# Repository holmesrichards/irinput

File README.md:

# Barton IR Input

This is a modified version, in Kosmo format, of the [Barton Musical Circuits 078 IR Input](https://www.bartonmusicalcircuits.com/irin/index.html) synth module. Barton describes the original version as follows:

> This module is designed to allow infrared light sources to interact with your synthesizer. The most common household sources of infrared light are fire and remote controls. Infrared LEDs are also readily available to DIYers who wanted to experiment with creating new devices for controlling synthesizers through this module.

The infrared phototransistor that picks up the IR light may be AC or DC coupled to the circuit. Outputs are a CV proportional to the IR signal and a gate that turns on when the CV rises above a threshold set with a panel pot. Another panel pot sets the phototransistor sensitivity.

Modifications to Barton's design are as follows:

* Added 3.5 mm TRS jack for a cable connecting to an external phototransistor and a switch to select internal or external PT. This allows using candles, lighters, etc. to control the synth while not having to have them right in front of it.
* Added gain knob to control gain of amplifier stage. The sensitivity pot (what Barton calls "bias") does vary the size of the signal but gives a small window between too small (no output) and too large (saturated). In AC coupled mode, the size of the AC component may be small, e.g. a few hundred mV, even when the sensitivity pot is set to just below saturation; of course the AC component disappears if the sensitivity pot is then raised further. The gain pot may be used to amplify the AC component to the level of a few volts. In AC mode, the gain range is 1 to 11. In DC mode, the gain pot may be used to help with faint IR sources; the gain range is 1 to 2.
* Added a bicolor indicator LED for the CV output. Brightness is indicative of CV amplitude and color indicates sign (which is positive in DC mode but can go negative in AC mode). 
* Added an indicator LED for saturation. This turns on when the PT emitter voltage is about 10 V. Normally one would want to operate with the sensitivity pot adjusted to just below where this LED comes on continuously while the IR light source is maximum.
* Specified A1M rather than B1M for sensitivity pot.

My modifications, PCB layout, and documentation are licensed Creative Commons Zero (see [LICENSE](LICENSE)). This license is not intended to apply to Michael Barton's intellectual property and no violation of any applicable copyright is intended. Do not use this design for any commercial purpose without first obtaining Barton's permission.

## Current draw
12 mA +12 V, 8 mA -12 V

## Photos

## Documentation

* [Schematic](Docs/irinput.pdf)
* PCB layout: [front](Docs/_layout_front.pdf), [back](Docs/_layout_back.pdf)
* [BOM](Docs/irinput_bom.md)
* [Build notes](Docs/irinput_build.md)
* [Blog post 1](https://analogoutputblog.wordpress.com/2022/02/22/playing-with-fire/), [blog post 2](https://analogoutputblog.wordpress.com/2022/03/27/ir-input/)

## GitHub repository

* [https://github.com/holmesrichards/irinput](https://github.com/holmesrichards/irinput)

## Submodules

This repo uses submodules aoKicad and Kosmo_panel, which provide needed libaries for KiCad. To clone:

```
git clone git@github.com:holmesrichards/ir_input.git
git submodule init
git submodule update
```

Alternatively do

```
git clone --recurse-submodules git@github.com:holmesrichards/ir_input.git
```

Or if you download the repository as a zip file, you must also click on the "aoKicad" and "Kosmo\_panel" links on the GitHub page (they'll have "@ something" after them) and download them as separate zip files which you can unzip into this repo's aoKicad and Kosmo\_panel directories.

If desired, copy the files from aoKicad and Kosmo\_panel to wherever you prefer (your KiCad user library directory, for instance, if you have one). Then in KiCad, add symbol libraries 

```
aoKicad/ao_symbols
Kosmo_panel/Kosmo
```
and footprint libraries 
```
aoKicad/ao_tht
Kosmo_panel/Kosmo_panel.
```

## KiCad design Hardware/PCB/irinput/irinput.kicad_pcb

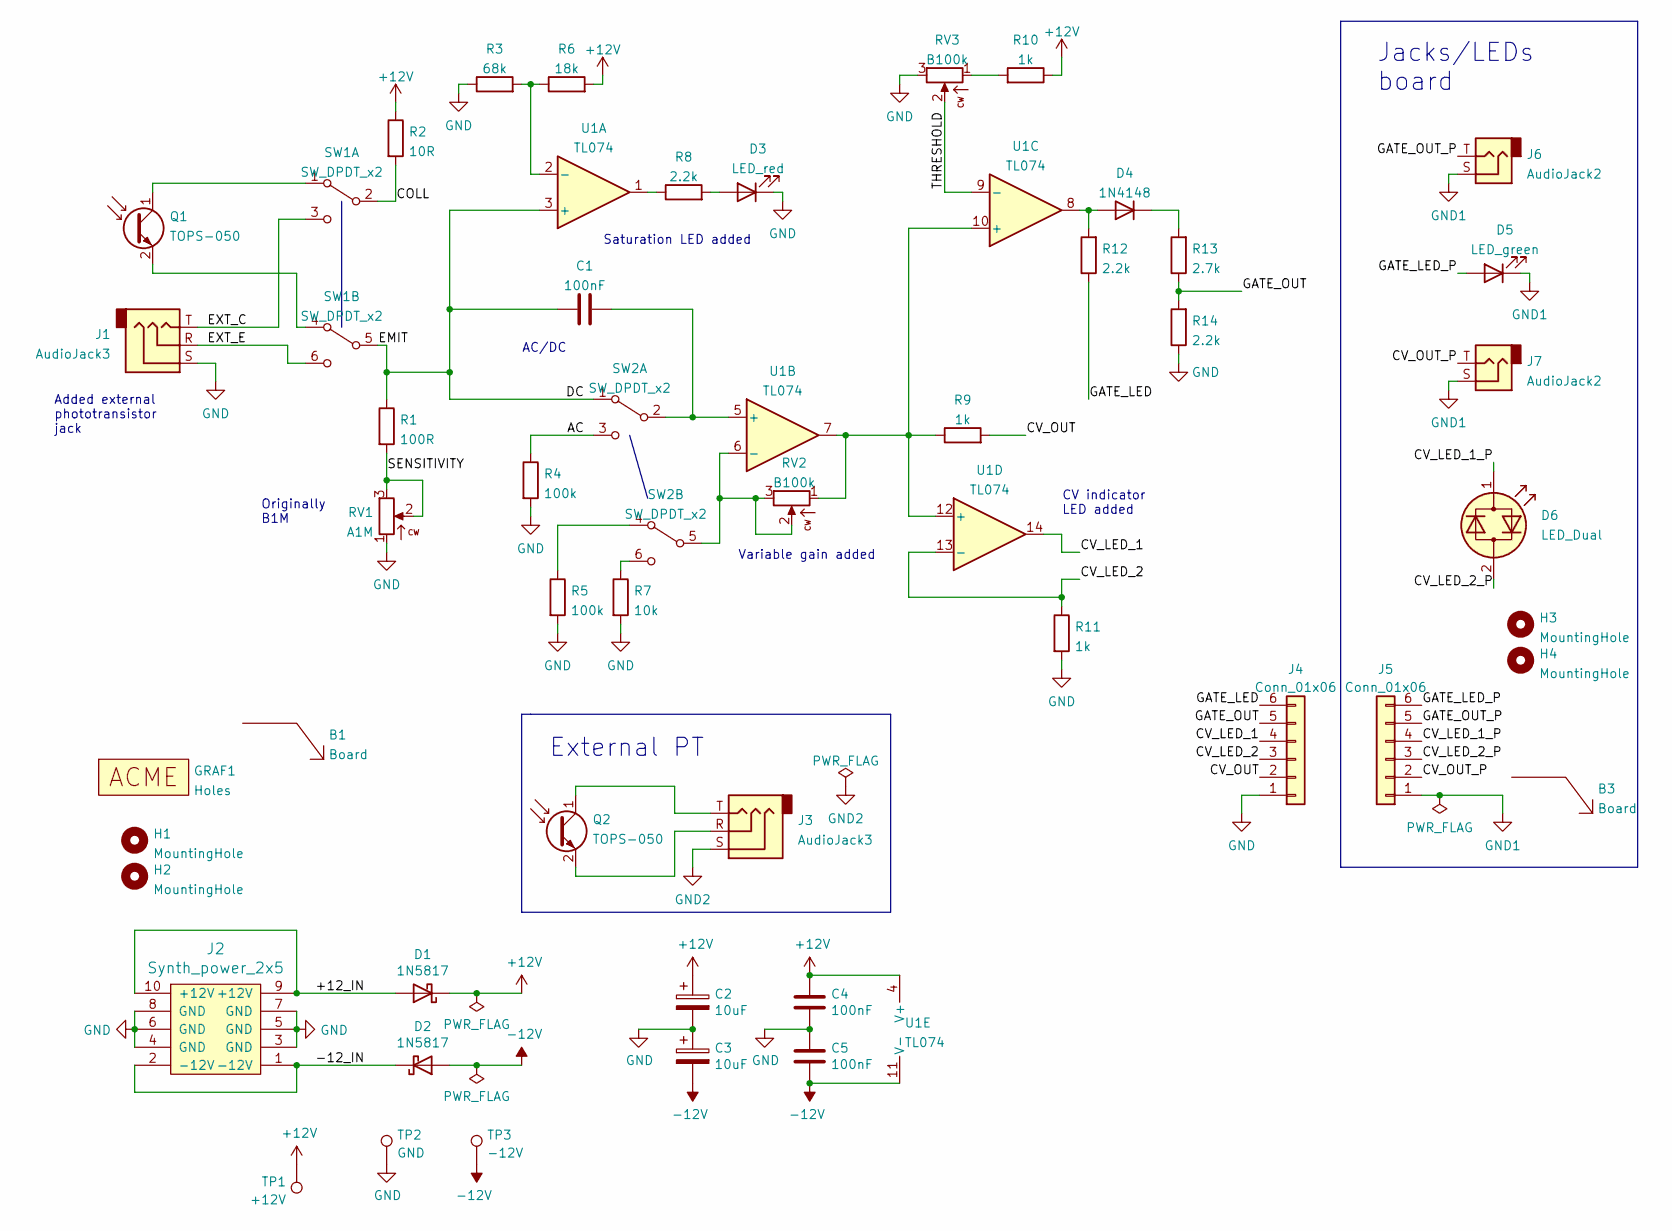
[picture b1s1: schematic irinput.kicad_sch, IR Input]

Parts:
B1, B3: Board; Board_Marker
C1: 100nF; C_Rect_L7.2mm_W2.5mm_P5.00mm_FKS2_FKP2_MKS2_MKP2
C2, C3: 10uF; CP_Radial_D6.3mm_P2.50mm
C4, C5: 100nF; C_Disc_D3.0mm_W1.6mm_P2.50mm
D1, D2: 1N5817; D_DO-41_SOD81_P10.16mm_Horizontal
D3: LED_red; LED_D5.0mm
D4: 1N4148; D_DO-35_SOD27_P7.62mm_Horizontal
D5: LED_green; LED_D5.0mm
D6: LED_Dual; LED_D5.0mm
GRAF1: Holes; irinput_panel_holes
H1, H2, H3, H4: MountingHole; MountingHole_3.2mm_M3
J1, J3: AudioJack3; Jack_3.5mm_PJ-301CM
J2: Synth_power_2x5; Power_Header
J4: Conn_01x06; PinHeader_1x06_P2.54mm_Vertical
J5: Conn_01x06; PinSocket_1x06_P2.54mm_Vertical
J6, J7: AudioJack2; Jack_6.35mm_PJ_629HAN
Q1, Q2: TOPS-050; LED_D5.0mm
R1: 100R; R_Axial_DIN0207_L6.3mm_D2.5mm_P10.16mm_Horizontal
R2: 10R; R_Axial_DIN0207_L6.3mm_D2.5mm_P10.16mm_Horizontal
R3: 68k; R_Axial_DIN0207_L6.3mm_D2.5mm_P10.16mm_Horizontal
R4, R5: 100k; R_Axial_DIN0207_L6.3mm_D2.5mm_P10.16mm_Horizontal
R6: 18k; R_Axial_DIN0207_L6.3mm_D2.5mm_P10.16mm_Horizontal
R7: 10k; R_Axial_DIN0207_L6.3mm_D2.5mm_P10.16mm_Horizontal
R8, R12, R14: 2.2k; R_Axial_DIN0207_L6.3mm_D2.5mm_P10.16mm_Horizontal
R9, R10, R11: 1k; R_Axial_DIN0207_L6.3mm_D2.5mm_P10.16mm_Horizontal
R13: 2.7k; R_Axial_DIN0207_L6.3mm_D2.5mm_P10.16mm_Horizontal
RV1: A1M; Potentiometer_Alpha_RD901F-40-00D_Single_Vertical_centered
RV2, RV3: B100k; Potentiometer_Alpha_RD901F-40-00D_Single_Vertical_centered
SW1, SW2: SW_DPDT_x2; DPDT-toggle-switch-1M-seriesx
TP1: +12V; TestPoint_THTPad_D1.5mm_Drill0.7mm
TP2: GND; TestPoint_THTPad_D1.5mm_Drill0.7mm
TP3: -12V; TestPoint_THTPad_D1.5mm_Drill0.7mm
U1: TL074; DIP-14_W7.62mm_Socket_LongPads

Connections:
+12V: C2.1, C4.1, D1.1 (K), R2.1, R6.2, R10.1, TP1.1, U1.4 (V+)
-12V: C3.2, C5.2, D2.2 (A), TP3.1, U1.11 (V-)
/+12_IN: D1.2 (A), J2.9 (+12V), J2.10 (+12V)
/-12_IN: D2.1 (K), J2.1 (-12V), J2.2 (-12V)
/AC: R4.1, SW2.3 (C)
/COLL: R2.2, SW1.2 (B)
/CV_LED_1: J4.4, U1.14
/CV_LED_1_P: D6.1 (KA), J5.4
/CV_LED_2: J4.3, R11.1, U1.13 (-)
/CV_LED_2_P: D6.2 (AK), J5.3
/CV_OUT: J4.2, R9.2
/CV_OUT_P: J5.2, J7.T
/DC: C1.1, R1.1, SW1.5 (B), SW2.1 (A), U1.3 (+)
/EXT_C: J1.T, SW1.3 (C)
/EXT_E: J1.R, SW1.6 (C)
/GATE_LED: J4.6, R12.1
/GATE_LED_P: D5.2 (A), J5.6
/GATE_OUT: J4.5, R13.1, R14.2
/GATE_OUT_P: J5.5, J6.T
/SENSITIVITY: R1.2, RV1.2, RV1.3
/THRESHOLD: RV3.2, U1.9 (-)
GND: C2.2, C3.1, C4.2, C5.1, D3.1 (K), J1.S, J2.3 (GND), J2.4 (GND), J2.5 (GND), J2.6 (GND), J2.7 (GND), J2.8 (GND), J4.1, R3.1, R4.2, R5.2, R7.2, R11.2, R14.1, RV1.1, RV3.3, TP2.1
GND1: D5.1 (K), J5.1, J6.S, J7.S
unnamed: C1.2, SW2.2 (B), U1.5 (+)
unnamed: D3.2 (A), R8.2
unnamed: D4.1 (K), R13.2
unnamed: D4.2 (A), R12.2, U1.8
unnamed: J3.R, Q2.2 (E)
unnamed: J3.T, Q2.1 (C)
unnamed: Q1.1 (C), SW1.1 (A)
unnamed: Q1.2 (E), SW1.4 (A)
unnamed: R3.2, R6.1, U1.2 (-)
unnamed: R5.1, SW2.4 (A)
unnamed: R7.1, SW2.6 (C)
unnamed: R8.1, U1.1
unnamed: R9.1, RV2.1, U1.7, U1.10 (+), U1.12 (+)
unnamed: R10.2, RV3.1
unnamed: RV2.2, RV2.3, SW2.5 (B), U1.6 (-)

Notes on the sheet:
External PT
Saturation LED added
AC/DC
Jacks/LEDs board
Variable gain added
Originally B1M
CV indicator LED added
Added external phototransistor jack

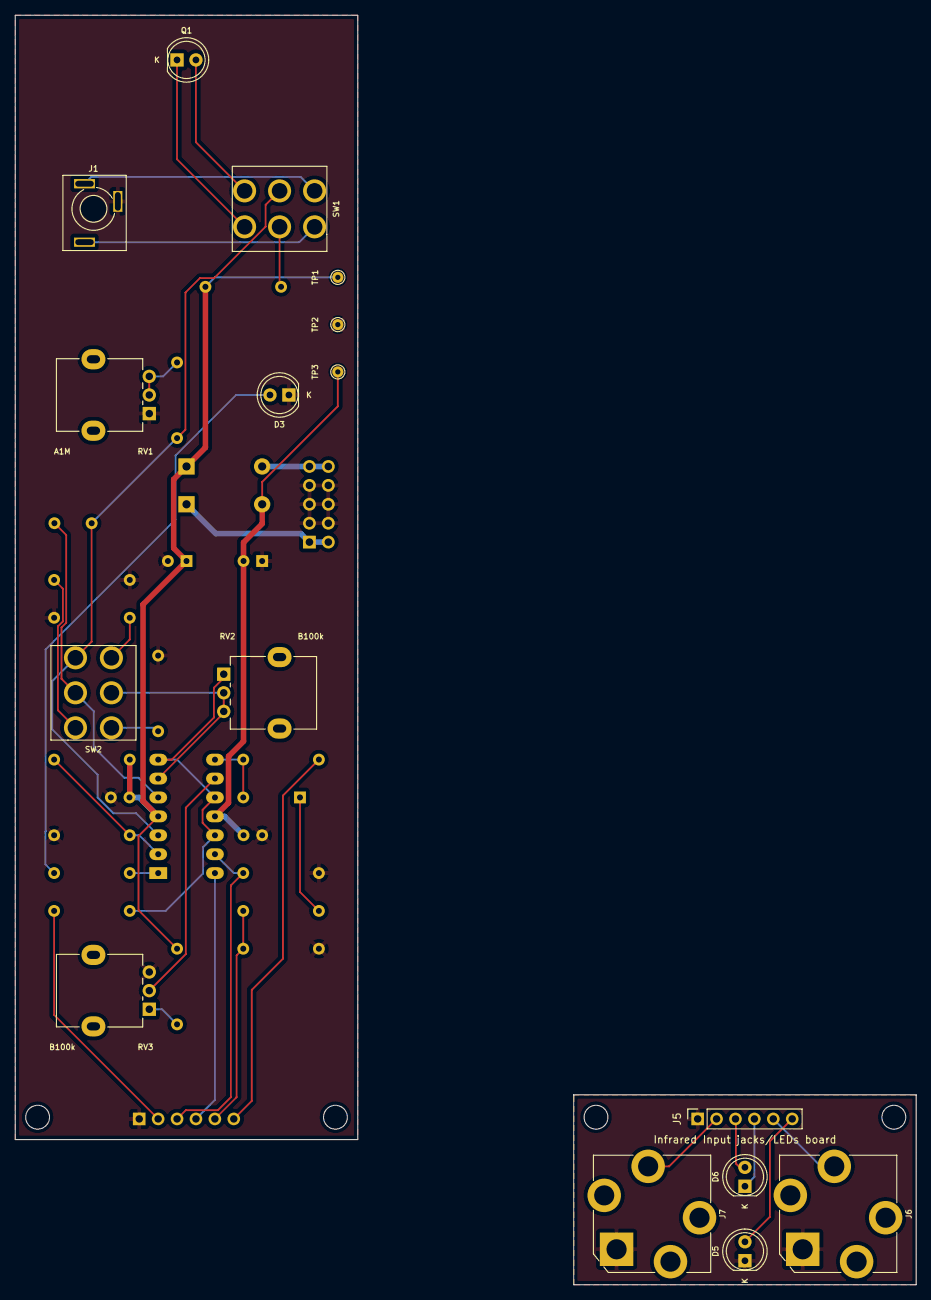
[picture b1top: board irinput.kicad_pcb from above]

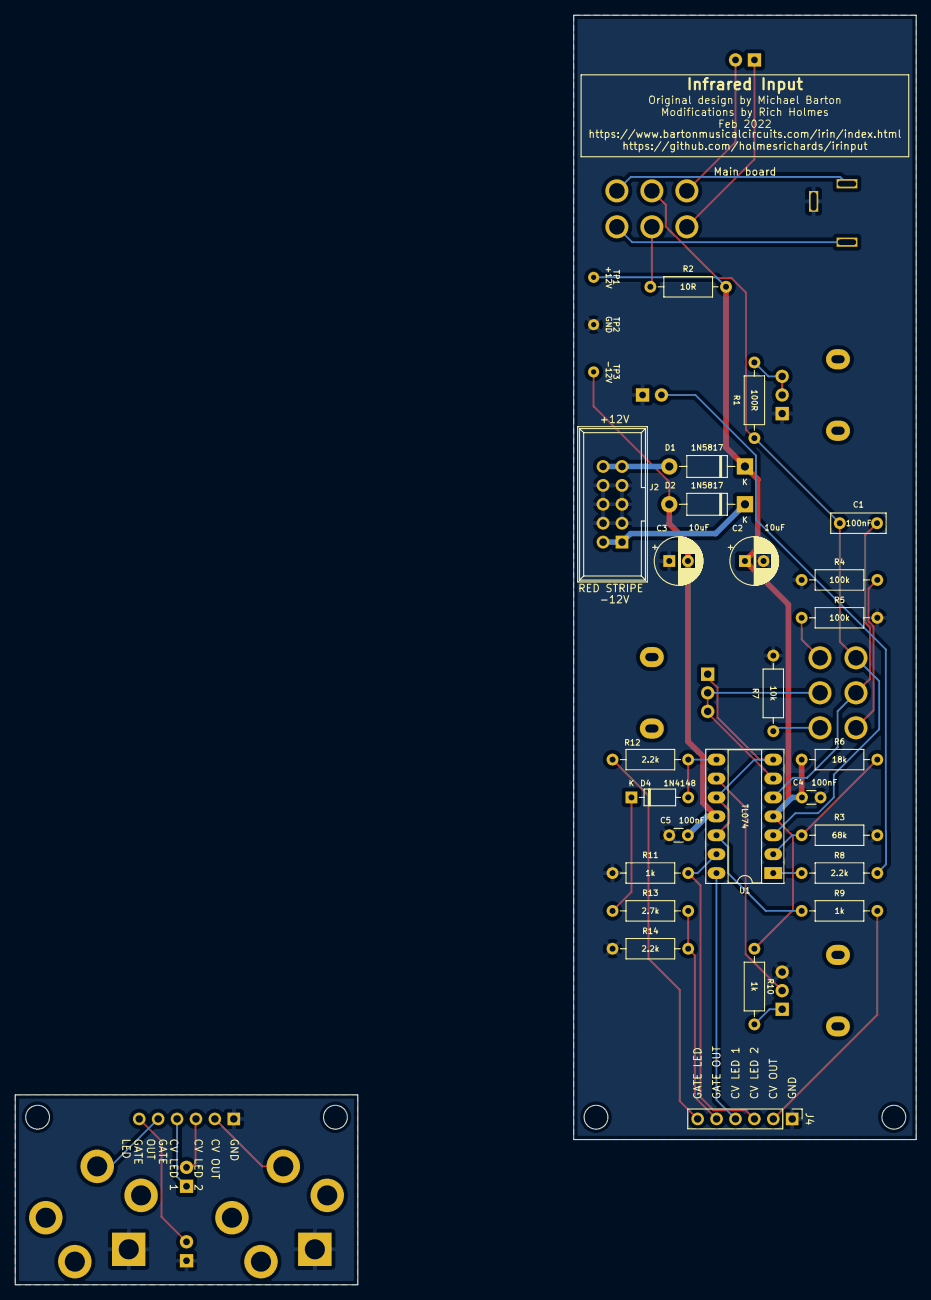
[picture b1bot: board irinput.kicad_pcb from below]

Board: 2 copper layers, 121.0 x 170.5 mm, 48 parts (25 on the bottom side), 36 nets.

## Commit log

2021-08-16 Initial version
2021-08-20 Panel design
2021-08-21 relocate libraries
2021-08-21 rm project libraries
2021-08-27 submodule doc
2021-09-15 SVG decontamination
2021-10-01 Expand label, move switch, add eye
2021-10-02 Library updates, panel design and Gerbers
2021-12-02 Panel art tweak
2021-12-25 README
2022-02-01 Better .gitignore
2022-02-10 Initial PCB design, revised panel, notes
2022-02-11 Revised schematic to buffer input to variable gain stage
2022-02-11 Revert to using no inverting stages, put gain control on non inverting stage. Add saturation LED.
2022-02-12 Corrections
2022-02-12 Corrected cap, initial BOM
2022-02-13 Silkscreen cleanup, revised panel
2022-03-27 Catch up to 1st fab run version
2022-03-27 Update libraries
2022-03-27 Create LICENSE
2022-03-27 License note
2022-03-27 Ext PT picture
2022-03-27 External PT notes
2022-05-12 Blog post links
